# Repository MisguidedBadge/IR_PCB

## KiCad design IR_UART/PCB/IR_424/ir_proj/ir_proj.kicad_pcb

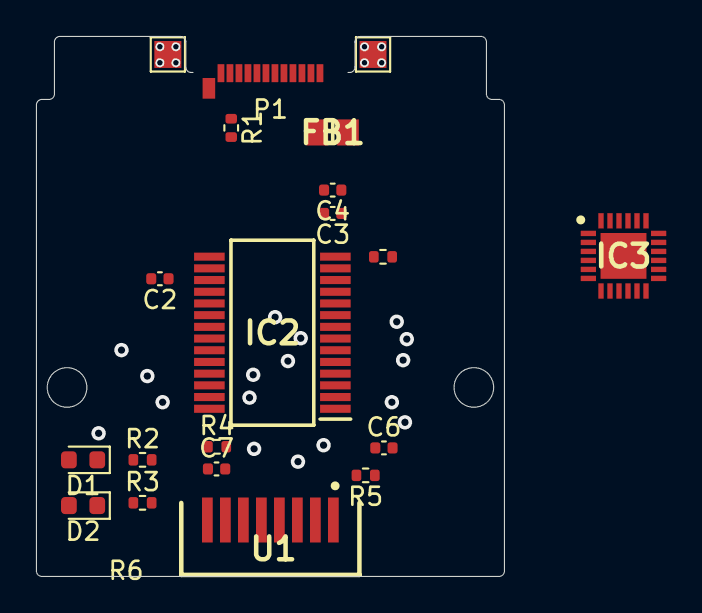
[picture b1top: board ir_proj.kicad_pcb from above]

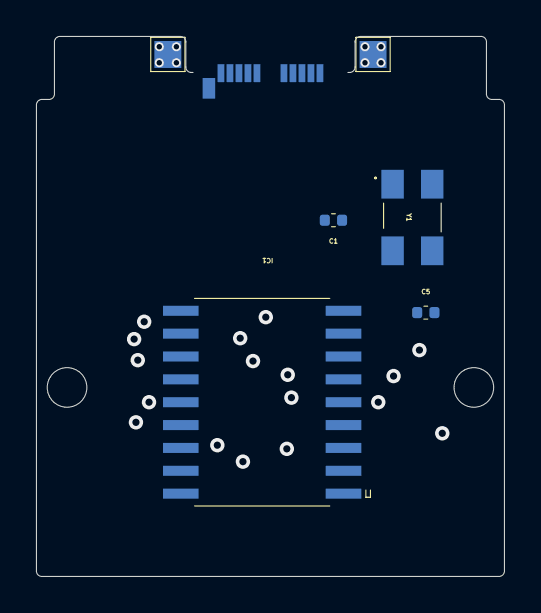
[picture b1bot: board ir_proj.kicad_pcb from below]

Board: 2 copper layers, 26.0 x 30.0 mm, 28 parts (6 on the bottom side), 27 nets, no tracks yet.

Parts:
C1, C5: 22pF; C_0402_1005Metric
C2, C3: 100nF; C_0402_1005Metric
C4, C6: 4.7uF; C_0402_1005Metric
C7: 0.1uF; C_0402_1005Metric
D1, D2: LED; LED_0603_1608Metric
FB1: FerriteBead; BEADC2012X110N
H1, H2: MountingHole; MountingHole_2.2mm_M2
IC1: MCP2150-I_SO; SOIC127P1030X265-18N
IC2: FT232RL-REEL; SOP65P778X200-28N
IC3: CP2102N-A02-GQFN24R; QFN50P400X400X80-25N-D
P1: USB_C_Plug; USB_C_Plug_Molex_105444
R1: 5.2k; R_0402_1005Metric
R2, R3: 270; R_0402_1005Metric
R4: 47; R_0402_1005Metric
R5: 0; R_0402_1005Metric
R6: 10k; R_0402_1005Metric
TP1, TP2, TP3, TP4: TestPoint; TestPoint_Pad_1.5x1.5mm
U1: TFDU4101-TR3
Y1: ECS-110.5-18-30B-AGN-TR; ECS11051830BAGNTR

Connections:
/3_3V: C2.1, IC2.17 (3V3OUT)
/CBUS0: IC2.23 (CBUS0), R2.2
/CBUS1: IC2.22 (CBUS1), R3.2
/CTS: IC1.12 (CTS), IC2.11 (CTS#)
/DCD: IC1.17 (CD), IC2.10 (DCD#)
/DM: IC2.16 (USBDM), P1.A6 (D+)
/DP: IC2.15 (USBDP), P1.A7 (D-)
/DSR: IC1.10 (DSR), IC2.9 (DSR#)
/DTR: IC1.11 (DTR), IC2.2 (DTR#)
/MCU_RX: IC1.8 (RX), IC2.1 (TXD)
/MCU_TX: IC1.7 (TX), IC2.5 (RXD)
/OSC1: C1.1, IC1.16 (OSC1/CLKIN), Y1.1 (IN/OUT)
/OSC2: C5.1, IC1.15 (OSC2), Y1.3 (OUT/IN)
/PWREN#: IC2.14 (CBUS3), R6.2
/RI: IC1.9 (RI), IC2.6 (RI#)
/RTS: IC1.13 (RTS), IC2.3 (RTS#)
/RXIR: IC1.3 (RXIR), U1.4
/RXLED: D2.1 (K), R3.1
/TXIR: IC1.2 (TXIR), U1.3
/TXLED: D1.1 (K), R2.1
/USB_VBUS: FB1.1, P1.A4 (VBUS), P1.A9 (VBUS), P1.B4 (VBUS), P1.B9 (VBUS)
/VCC: C3.2, C4.2, C6.1, FB1.2, IC1.14 (VDD), IC2.20 (VCC), R4.1, R5.1
/VCCIO: D1.2 (A), D2.2 (A), IC2.4 (VCCIO), R6.1
GND: C1.2, C2.2, C3.1, C4.1, C5.2, C6.2, C7.1, IC1.1 (BAUD0), IC1.5 (VSS), IC1.18 (BAUD1), IC2.7 (GND_1), IC2.18 (GND_2), IC2.21 (GND_3), IC2.25 (AGND), IC2.26 (TEST), P1.A1 (GND), P1.A12 (GND), P1.B1 (GND), P1.B12 (GND), P1.S1 (SHIELD), R1.2, TP1.1, TP2.1, TP3.1, TP4.1, U1.5, U1.8, Y1.2 (GND_1), Y1.4 (GND_2)
unnamed: C7.2, R4.2, U1.6
unnamed: P1.A5 (CC), R1.1
unnamed: R5.2, U1.1

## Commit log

2022-07-17 Init

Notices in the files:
IR_UART/PCB/IR_424/ir_proj/ir_proj.kicad_pcb:
This work is licensed under a Creative Commons Attribution 4.0 International License
